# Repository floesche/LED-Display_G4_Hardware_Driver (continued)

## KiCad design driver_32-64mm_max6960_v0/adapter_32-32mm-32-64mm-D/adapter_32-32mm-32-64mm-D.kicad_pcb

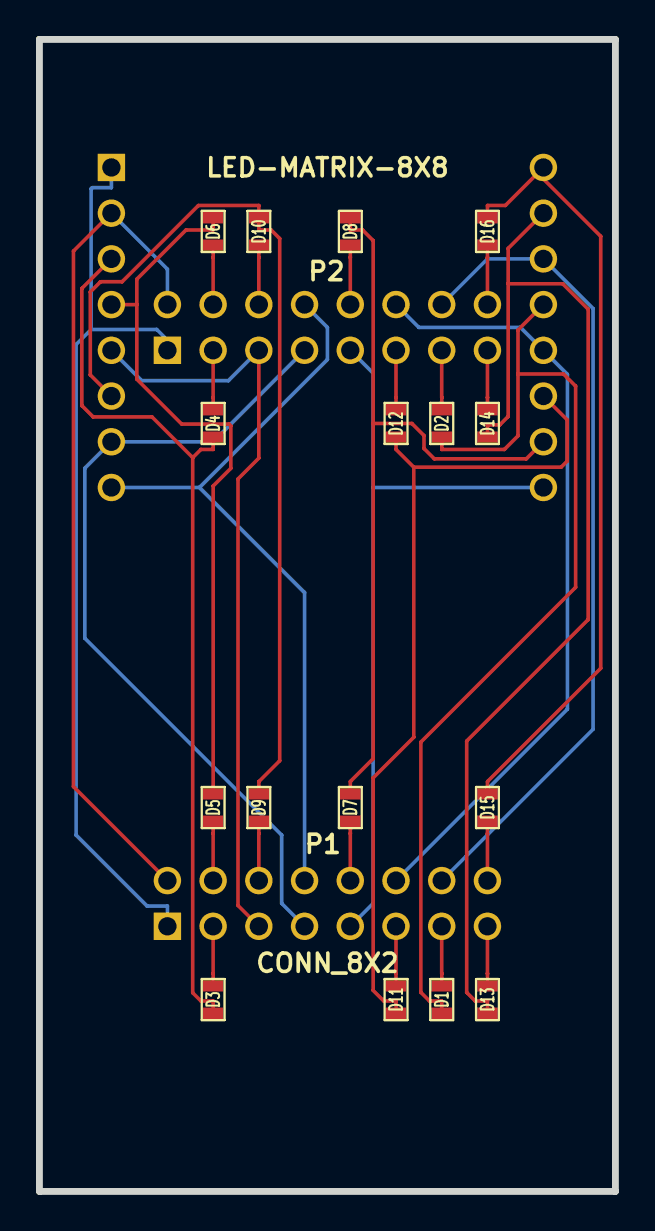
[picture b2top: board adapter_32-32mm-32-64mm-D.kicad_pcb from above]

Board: 2 copper layers, 32.0 x 64.0 mm, 19 parts (0 on the bottom side), 32 nets.

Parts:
D1, D2, D3, D4, D5, D6, D7, D8, D9, D10, D11, D12, D13, D14, D15, D16: DIODE; SM0603
M1: LED-MATRIX-8X8; LED_8x8
P1, P2: CONN_8X2; pin_array_8x2_custom

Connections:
/COL1: D1.1, P1.13
/COL2: D3.1, P1.3
/COL3: D5.1, P1.4
/COL4: D7.1, P1.10
/COL5: D9.1, P1.6
/COL6: D11.1, P1.11
/COL7: D13.1, P1.15
/COL8: D15.1, P1.16
/COL9: D2.1, P2.13
/COL10: D4.1, P2.3
/COL11: D6.1, P2.4
/COL12: D8.1, P2.10
/COL13: D10.1, P2.6
/COL14: D12.1, P2.11
/COL15: D14.1, P2.15
/COL16: D16.1, P2.16
/ROW1: M1.9, P1.9, P2.9
/ROW2: M1.14, P1.14, P2.14
/ROW3: M1.8, P1.8, P2.8
/ROW4: M1.12, P1.12, P2.12
/ROW5: M1.1, P1.1, P2.1
/ROW6: M1.7, P1.7, P2.7
/ROW7: M1.2, P1.2, P2.2
/ROW8: M1.5, P1.5, P2.5
unnamed: D5.2, D6.2, M1.4
unnamed: D15.2, D16.2, M1.16
unnamed: D13.2, D14.2, M1.15
unnamed: D11.2, D12.2, M1.11
unnamed: D7.2, D8.2, M1.10
unnamed: D3.2, D4.2, M1.3
unnamed: D1.2, D2.2, M1.13
unnamed: D9.2, D10.2, M1.6

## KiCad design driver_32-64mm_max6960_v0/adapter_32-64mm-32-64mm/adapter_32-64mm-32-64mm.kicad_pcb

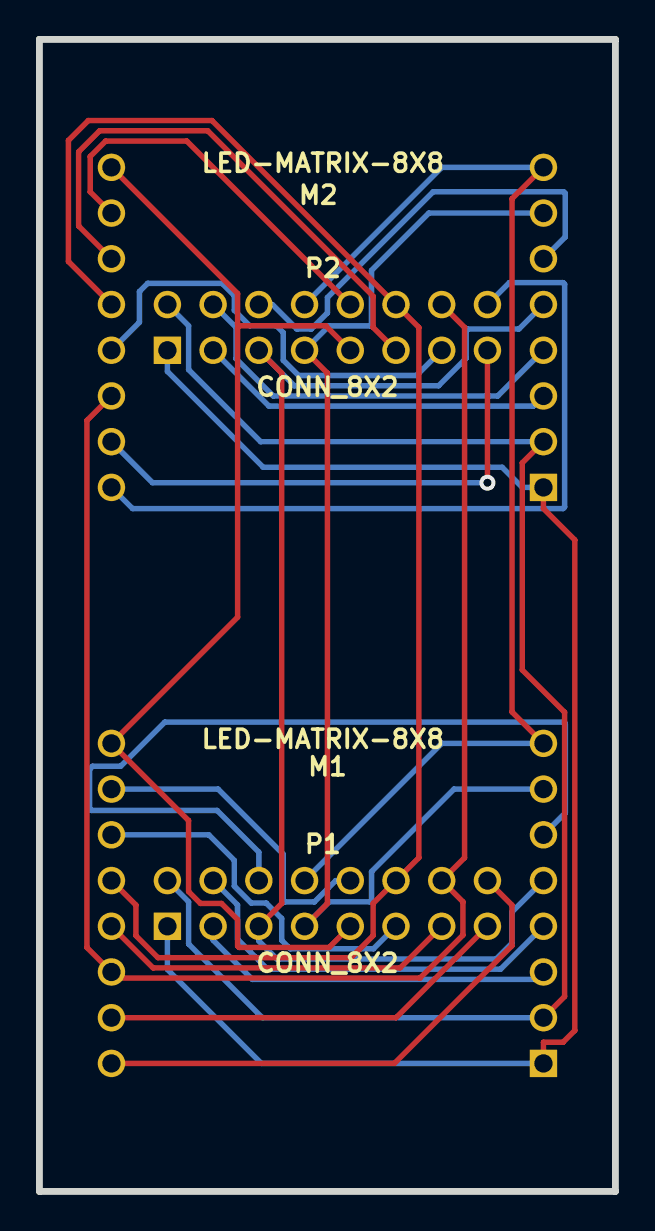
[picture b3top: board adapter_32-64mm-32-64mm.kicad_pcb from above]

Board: 2 copper layers, 32.0 x 64.0 mm, 4 parts (0 on the bottom side), 24 nets.

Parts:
M1, M2: LED-MATRIX-8X8; LED_8x8
P1, P2: CONN_8X2; pin_array_8x2_custom

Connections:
/COL1: M1.13, P1.13
/COL2: M1.3, P1.3
/COL3: M1.4, P1.4
/COL4: M1.10, P1.10
/COL5: M1.6, P1.6
/COL6: M1.11, P1.11
/COL7: M1.15, P1.15
/COL8: M1.16, P1.16
/COL9: M2.13, P2.13
/COL10: M2.3, P2.3
/COL11: M2.4, P2.4
/COL12: M2.10, P2.10
/COL13: M2.6, P2.6
/COL14: M2.11, P2.11
/COL15: M2.15, P2.15
/COL16: M2.16, P2.16
/ROW1: M1.9, M2.9, P1.9, P2.9
/ROW2: M1.14, M2.14, P1.14, P2.14
/ROW3: M1.8, M2.8, P1.8, P2.8
/ROW4: M1.12, M2.12, P1.12, P2.12
/ROW5: M1.1, M2.1, P1.1, P2.1
/ROW6: M1.7, M2.7, P1.7, P2.7
/ROW7: M1.2, M2.2, P1.2, P2.2
/ROW8: M1.5, M2.5, P1.5, P2.5

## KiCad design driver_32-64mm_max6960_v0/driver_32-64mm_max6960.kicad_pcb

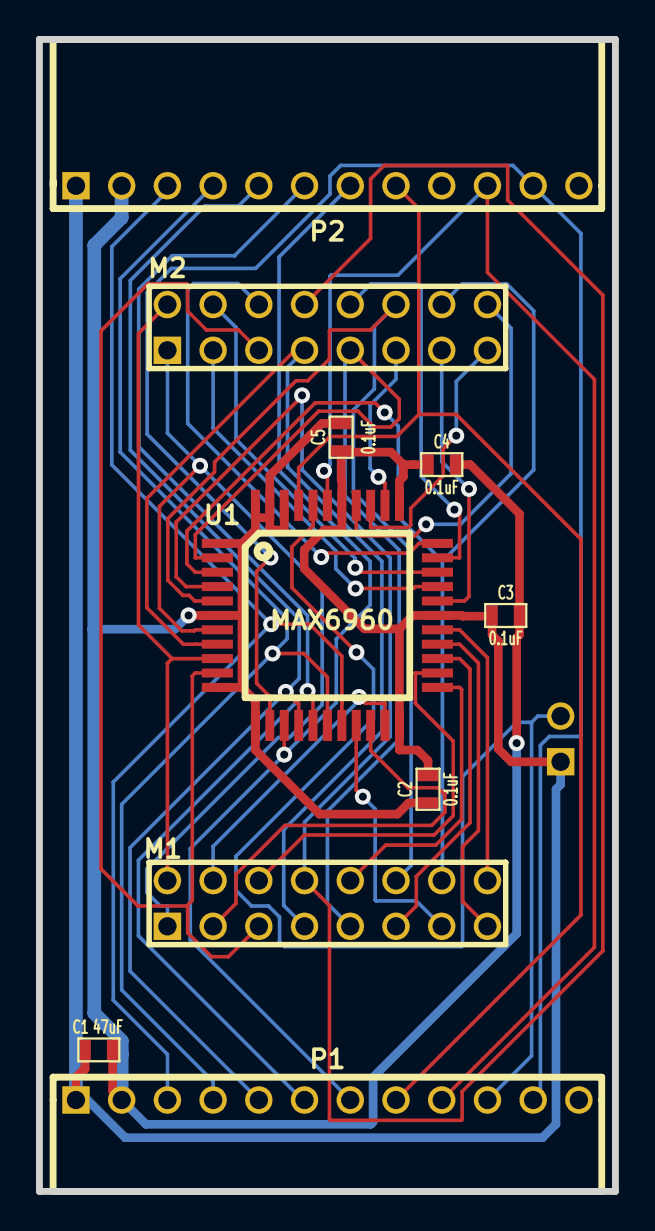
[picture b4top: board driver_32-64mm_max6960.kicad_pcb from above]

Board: 2 copper layers, 32.0 x 64.0 mm, 11 parts (1 on the bottom side), 35 nets.

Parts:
C1: 47uF; SM0603
C2, C3, C4, C5: 0.1uF; SM0603
M1, M2: LED-MATRIX-8X8; pin_array_8x2
P1: CONN_12; HEADER_BOT
P2: CONN_12; HEADER_TOP
P3: CONN_2; PIN_ARRAY_2X1
U1: MAX6960; MQFP44

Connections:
/ADDCLK: P1.8, P2.8, U1.41
/ADDIN: P1.10, P3.2, U1.40
/ADDOUT: P1.9, P2.10, U1.39
/CLK: P1.4, P2.4, U1.17
/COL1: M1.13, U1.19
/COL2: M1.3, U1.20
/COL3: M1.4, U1.21
/COL4: M1.10, U1.23
/COL5: M1.6, U1.24
/COL6: M1.11, U1.25
/COL7: M1.15, U1.26
/COL8: M1.16, U1.27
/COL9: M2.13, U1.29
/COL10: M2.3, U1.30
/COL11: M2.4, U1.31
/COL12: M2.10, U1.32
/COL13: M2.6, U1.33
/COL14: M2.11, U1.35
/COL15: M2.15, U1.36
/COL16: M2.16, U1.37
/CS: P1.7, P2.7, U1.14
/MISO: P1.6, P2.6, U1.16
/MOSI: P1.5, P2.5, U1.15
/OSC: P1.11, P2.11, U1.13
/ROW1: M1.9, M2.9, U1.2
/ROW2: M1.14, M2.14, U1.3
/ROW3: M1.8, M2.8, U1.4
/ROW4: M1.12, M2.12, U1.5
/ROW5: M1.1, M2.1, U1.7
/ROW6: M1.7, M2.7, U1.8
/ROW7: M1.2, M2.2, U1.9
/ROW8: M1.5, M2.5, U1.10
/RST: P1.3, P2.3, U1.18
/V+: C1.1, C2.1, C3.1, C4.1, C5.1, P1.1, P2.1, P3.1, U1.22, U1.28, U1.34, U1.38
GND: C1.2, C2.2, C3.2, C4.2, C5.2, P1.2, P2.2, U1.1, U1.6, U1.11, U1.12, U1.42, U1.43, U1.44

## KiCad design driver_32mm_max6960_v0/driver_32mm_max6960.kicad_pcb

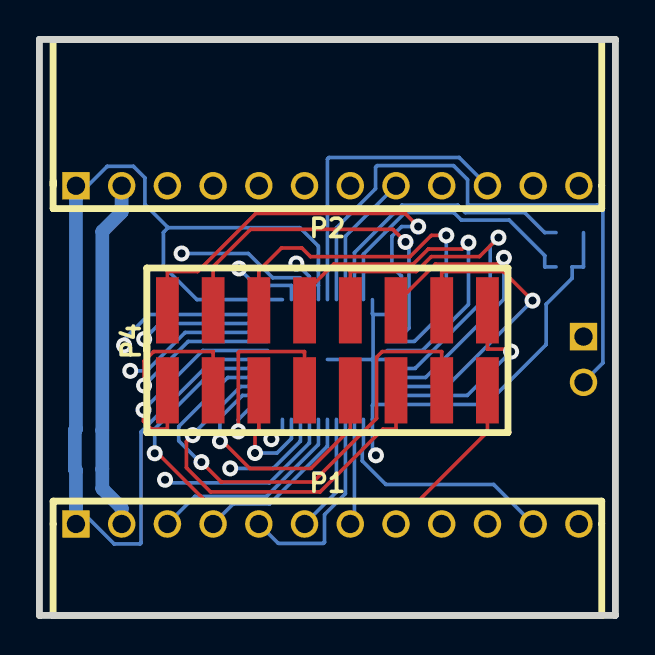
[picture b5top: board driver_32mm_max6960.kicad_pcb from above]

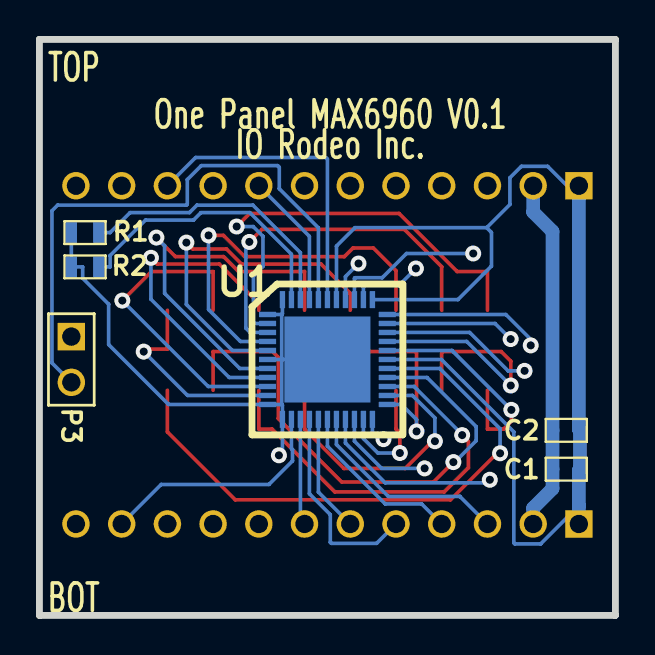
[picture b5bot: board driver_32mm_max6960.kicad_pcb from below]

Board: 4 copper layers, 32.0 x 32.0 mm, 9 parts (6 on the bottom side), 29 nets.

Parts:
C1: 47uF; SM0603
C2: 0.1uF; SM0603
P1: CONN_12; HEADER_BOT
P2: CONN_12; HEADER_TOP
P3: CONN_2; PIN_ARRAY_2X1
P4: CONN_8X2; SMD_HEADER_8X2
R1, R2: R; SM0603
U1: MAX6960; T4477-3

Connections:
/ADDCLK: P1.8, P2.8, U1.41
/ADDIN: P1.10, P3.2, U1.40
/ADDOUT: P1.9, P2.10, U1.39
/CLK: P1.4, P2.4, U1.17
/COL1: P4.1, U1.19, U1.29
/COL10: P4.3, U1.20, U1.30
/COL11: P4.5, U1.21, U1.31
/COL12: P4.7, U1.23, U1.32
/COL13: P4.9, U1.24, U1.33
/COL14: P4.11, U1.25, U1.35
/COL15: P4.13, U1.26, U1.36
/COL16: P4.15, U1.27, U1.37
/CS: P1.7, P2.7, U1.14
/MISO: P1.6, P2.6, U1.16
/MOSI: P1.5, P2.5, U1.15
/OSC: P1.11, P2.11, U1.13
/ROW1: P4.2, U1.2
/ROW2: P4.4, U1.3
/ROW3: P4.6, U1.4
/ROW4: P4.8, U1.5
/ROW5: P4.10, U1.7
/ROW6: P4.12, U1.8
/ROW7: P4.14, U1.9
/ROW8: P4.16, U1.10
/RST: P1.3, P2.3, U1.18
/V+: C1.1, C2.1, P1.1, P2.1, P3.1, U1.22, U1.28, U1.34, U1.38
GND: C1.2, C2.2, P1.2, P2.2, R1.2, R2.2, U1.1, U1.6, U1.11, U1.12, U1.44, U1.45
unnamed: R2.1, U1.43
unnamed: R1.1, U1.42

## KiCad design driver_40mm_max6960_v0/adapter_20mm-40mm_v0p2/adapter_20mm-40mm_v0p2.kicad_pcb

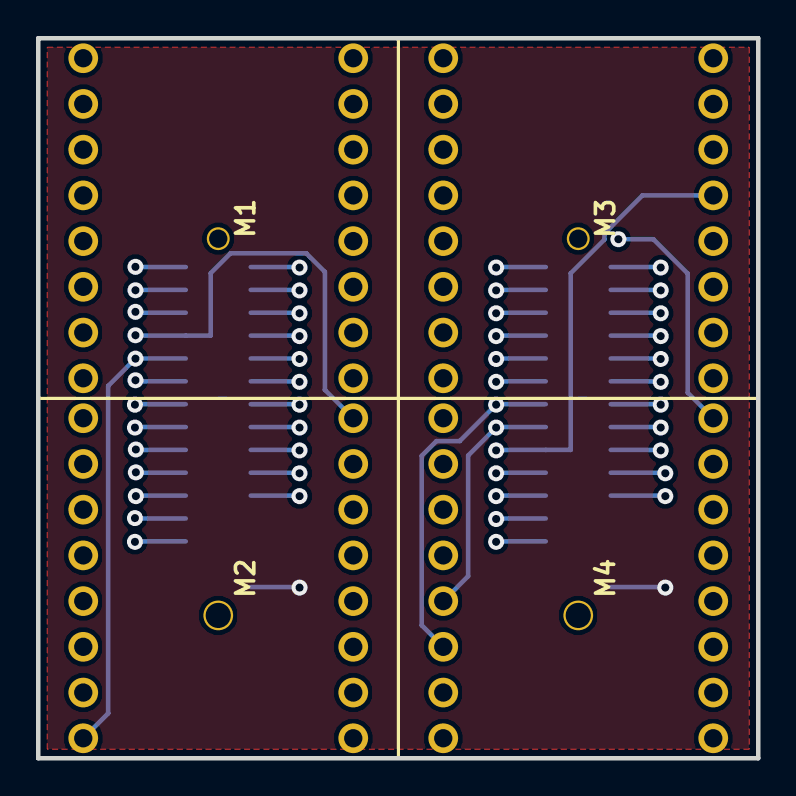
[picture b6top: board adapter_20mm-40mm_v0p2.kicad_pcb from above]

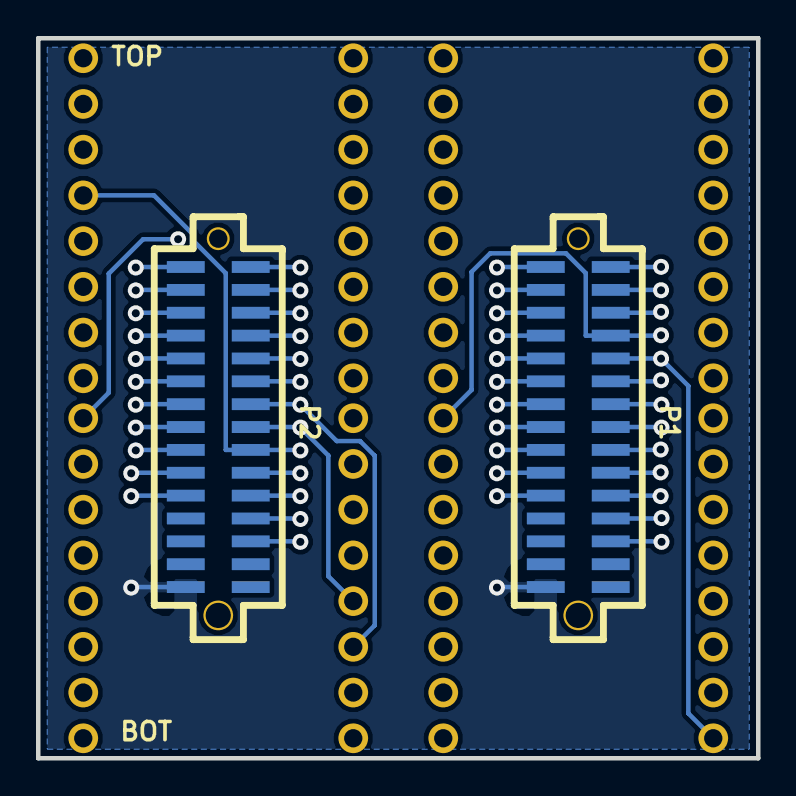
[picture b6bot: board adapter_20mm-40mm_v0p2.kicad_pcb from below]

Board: 4 copper layers, 40.0 x 40.0 mm, 6 parts (2 on the bottom side), 49 nets.

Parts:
M1, M2, M3, M4: BETLUX-LED-8X8_C; LED_MATRIX_20MM_8x8
P1, P2: CONN15X2; SMD_PIN_ARRAY_F_0P5IN_15X2

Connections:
/COL_A1: M1.5, P1.18
/COL_A2: M1.6, P1.20
/COL_A3: M1.7, P1.22
/COL_A4: M1.8, P1.25
/COL_A5: M1.16, P1.23
/COL_A6: M1.15, P1.21
/COL_A7: M1.14, P1.19
/COL_A8: M1.13, P1.17
/COL_A9: M2.5, P1.15
/COL_A10: M2.6, P1.13
/COL_A11: M2.7, P1.11
/COL_A12: M2.8, P1.9
/COL_A13: M2.16, P1.7
/COL_A14: M2.15, P1.5
/COL_A15: M2.14, P1.3
/COL_A16: M2.13, P1.1
/COL_B1: M3.5, P2.18
/COL_B2: M3.6, P2.20
/COL_B3: M3.7, P2.22
/COL_B4: M3.8, P2.25
/COL_B5: M3.16, P2.23
/COL_B6: M3.15, P2.21
/COL_B7: M3.14, P2.19
/COL_B8: M3.13, P2.17
/COL_B9: M4.5, P2.15
/COL_B10: M4.6, P2.13
/COL_B11: M4.7, P2.11
/COL_B12: M4.8, P2.9
/COL_B13: M4.16, P2.7
/COL_B14: M4.15, P2.5
/COL_B15: M4.14, P2.3
/COL_B16: M4.13, P2.1
/ROW_A1: M1.1, M2.1, P1.2
/ROW_A2: M1.2, M2.2, P1.4
/ROW_A3: M1.3, M2.3, P1.6
/ROW_A4: M1.4, M2.4, P1.8
/ROW_A5: M1.12, M2.12, P1.10
/ROW_A6: M1.11, M2.11, P1.12
/ROW_A7: M1.10, M2.10, P1.14
/ROW_A8: M1.9, M2.9, P1.16
/ROW_B1: M3.1, M4.1, P2.2
/ROW_B2: M3.2, M4.2, P2.4
/ROW_B3: M3.3, M4.3, P2.6
/ROW_B4: M3.4, M4.4, P2.8
/ROW_B5: M3.12, M4.12, P2.10
/ROW_B6: M3.11, M4.11, P2.12
/ROW_B7: M3.10, M4.10, P2.14
/ROW_B8: M3.9, M4.9, P2.16
GND: P1.30, P2.30

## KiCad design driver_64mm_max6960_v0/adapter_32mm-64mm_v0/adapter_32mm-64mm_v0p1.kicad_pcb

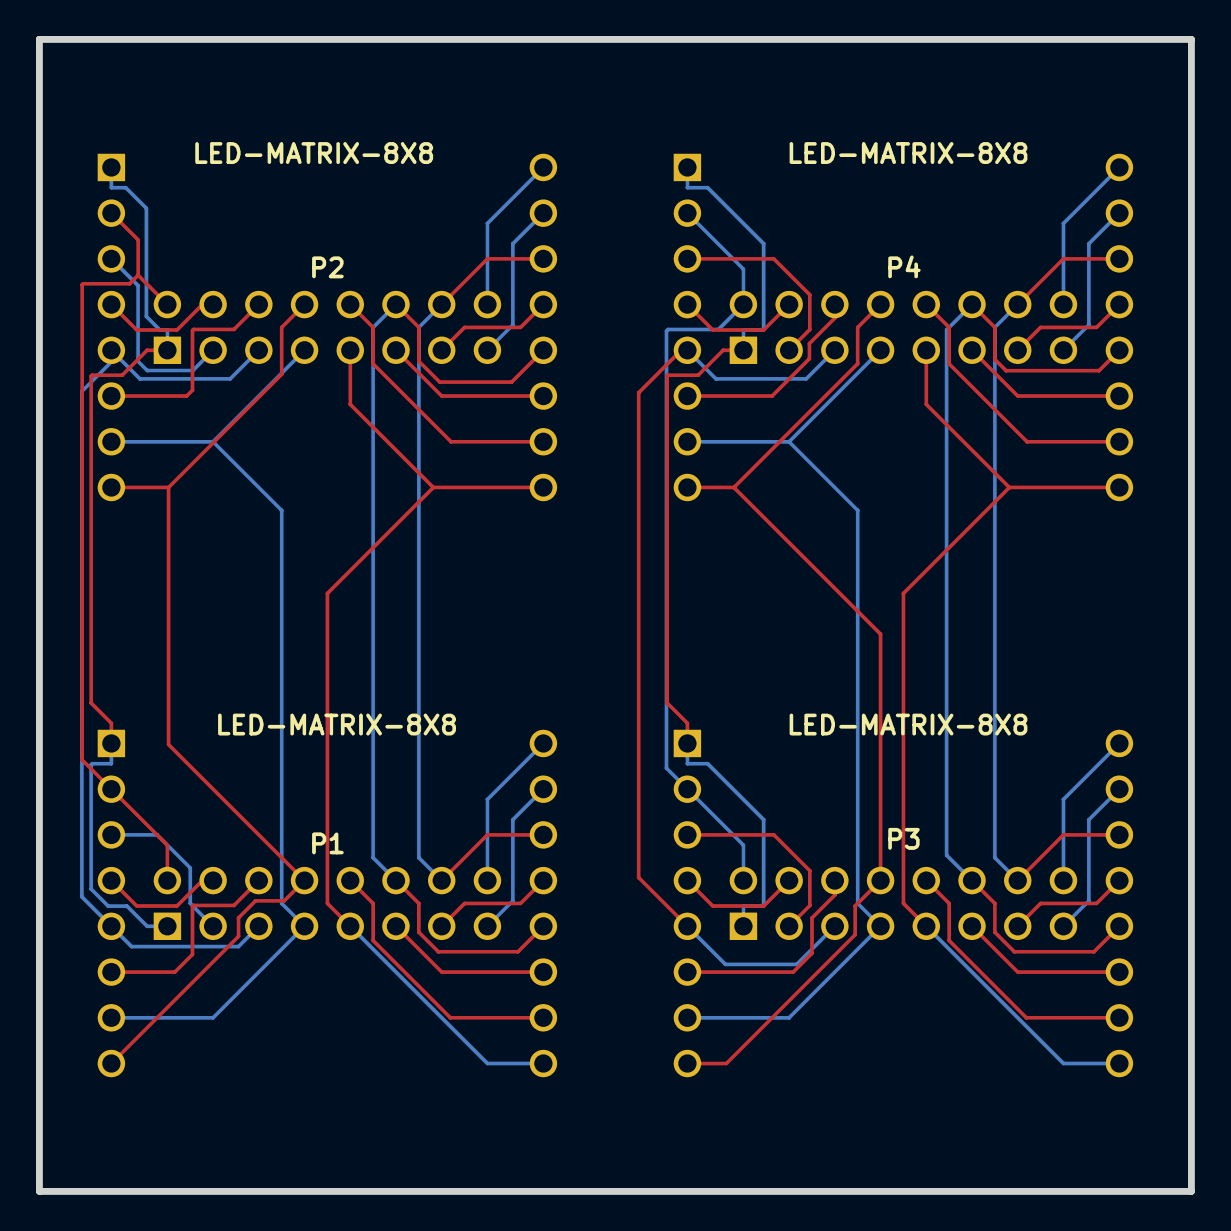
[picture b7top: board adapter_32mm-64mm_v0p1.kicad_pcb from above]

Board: 2 copper layers, 64.0 x 64.0 mm, 8 parts (0 on the bottom side), 48 nets.

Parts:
M1, M2, M3, M4: LED-MATRIX-8X8; LED_8x8
P1, P2, P3, P4: CONN_8X2; pin_array_8x2_custom

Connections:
/COL_A1: M1.13, P1.13
/COL_A2: M1.3, P1.3
/COL_A3: M1.4, P1.4
/COL_A4: M1.10, P1.10
/COL_A5: M1.6, P1.6
/COL_A6: M1.11, P1.11
/COL_A7: M1.15, P1.15
/COL_A8: M1.16, P1.16
/COL_A9: M2.13, P2.13
/COL_A10: M2.3, P2.3
/COL_A11: M2.4, P2.4
/COL_A12: M2.10, P2.10
/COL_A13: M2.6, P2.6
/COL_A14: M2.11, P2.11
/COL_A15: M2.15, P2.15
/COL_A16: M2.16, P2.16
/COL_B1: M3.13, P3.13
/COL_B2: M3.3, P3.3
/COL_B3: M3.4, P3.4
/COL_B4: M3.10, P3.10
/COL_B5: M3.6, P3.6
/COL_B6: M3.11, P3.11
/COL_B7: M3.15, P3.15
/COL_B8: M3.16, P3.16
/COL_B9: M4.13, P4.13
/COL_B10: M4.3, P4.3
/COL_B11: M4.4, P4.4
/COL_B12: M4.10, P4.10
/COL_B13: M4.6, P4.6
/COL_B14: M4.11, P4.11
/COL_B15: M4.15, P4.15
/COL_B16: M4.16, P4.16
/ROW_A1: M1.9, M2.9, P1.9, P2.9
/ROW_A2: M1.14, M2.14, P1.14, P2.14
/ROW_A3: M1.8, M2.8, P1.8, P2.8
/ROW_A4: M1.12, M2.12, P1.12, P2.12
/ROW_A5: M1.1, M2.1, P1.1, P2.1
/ROW_A6: M1.7, M2.7, P1.7, P2.7
/ROW_A7: M1.2, M2.2, P1.2, P2.2
/ROW_A8: M1.5, M2.5, P1.5, P2.5
/ROW_B1: M3.9, M4.9, P3.9, P4.9
/ROW_B2: M3.14, M4.14, P3.14, P4.14
/ROW_B3: M3.8, M4.8, P3.8, P4.8
/ROW_B4: M3.12, M4.12, P3.12, P4.12
/ROW_B5: M3.1, M4.1, P3.1, P4.1
/ROW_B6: M3.7, M4.7, P3.7, P4.7
/ROW_B7: M3.2, M4.2, P3.2, P4.2
/ROW_B8: M3.5, M4.5, P3.5, P4.5

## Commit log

2020-08-06 initial commit, as received from jET
2020-08-10 add eagle file
2020-08-13 update to mm based GRB for V1, generated today
2020-08-13 updating readme
2020-08-17 define version 1.2, restructure paths
2020-08-27 update panel v1
2020-08-27 reorganize production folder
2020-08-31 update BOM, add paste layer
2020-09-11 update paste
2020-09-12 reorganize docu
2020-09-26 separate github and gh-pages content
2020-09-30 moved documentation from central repo
2020-10-02 update link
2020-10-21 update documentation popups
2020-10-28 add toc
2020-11-11 generated G4.1.6
2020-11-11 rename schematic file
2020-11-12 received design file from jET, generated fabrication files from that
2021-07-27 update version
2021-11-15 update driver description
2021-11-15 fix KiCad files
2021-11-15 v0p4
2021-11-15 update v0p4
2021-11-15 v0p5
2021-11-15 add v0p3
2021-11-15 consistent file name
2021-11-15 add driver v0p2
2021-11-15 move atmel driver here
2021-11-15 add 32mm driver
2021-11-15 add v0p2
2021-11-15 add 32mm v0p2
2021-11-15 file naming
2021-11-15 fix links
2021-11-15 move max6960 here
2021-11-15 add max6960 32mm driver
2021-11-15 consistent file naming
2021-11-15 add adapters to 40mm max
2021-11-16 add driver 32mm max6960
2021-11-16 add adapter for 32mm max
2021-11-16 add two-panel max version
2021-11-16 add adapters
2021-11-16 add diode adapter
2021-11-19 add license, fix text
2021-11-19 better imgage captions
2021-11-30 consistent documentation
2022-10-28 top silkscreen without feet
2022-10-28 new version → documentation
2022-11-30 fix typo
2023-07-31 Added design files for new v0.5 driver design.
2023-08-07 Changing new driver version number from v0p5 to v1p9.
2023-08-07 More modes having to do with chaning version number to v1.9.
2023-08-07 Some cleanup. Changed silkscreen to new v1.9. Need to remake gerbers.
2023-08-07 Remade gerber files. Added some dummy BOM and CPL file to help check component orientations.
2023-08-09 Finished correcting/verifying the orientations of JLCPCB sourced components.
2023-08-21 generate v1.9.3
2023-08-21 submitted files for production
